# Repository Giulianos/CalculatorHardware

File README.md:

# Programmable Pocket Calculator Hardware

## Description
This programmable pocket sized calculator has the following features:
  - Credit card size, 8mm thick!
  - ARM Cortex M4 Microcontroller
  - microSD card reader
  - OLED Display
  - 44 mechanical* matrix keyboard (*tactile switches)
  - Lipo battery charging circuit

## Images
- Unsoldered, showing it's thickness

- Soldered

- Front view of PCB without tactile switches and with OLED in place

- Back view of PCB unsoldered with battery, micro usb and micro sd card reader in place

- Altium's 3D Render of the PCB

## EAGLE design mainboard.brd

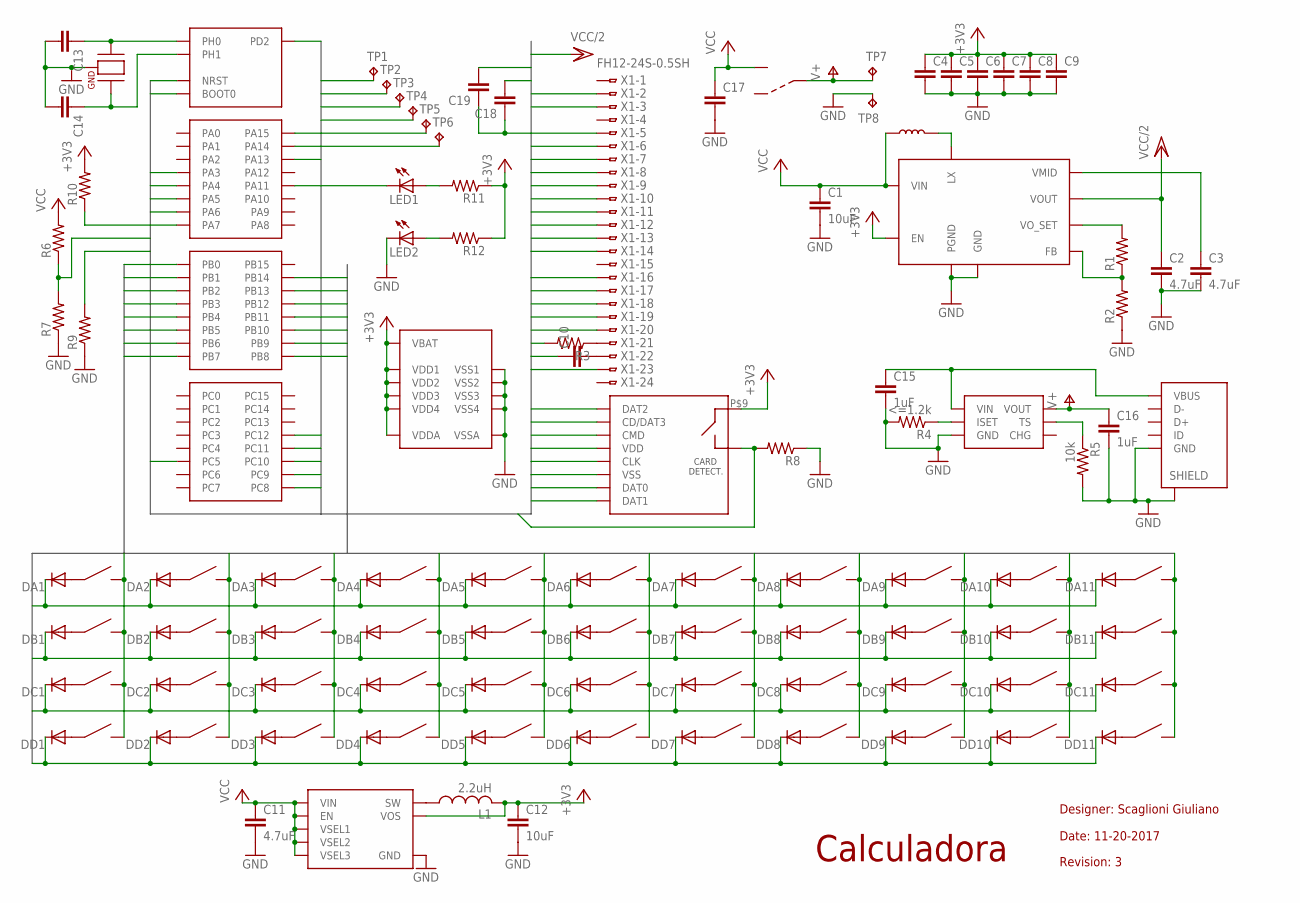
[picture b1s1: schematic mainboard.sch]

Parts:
BTA1, BTA2, BTA3, BTA4, BTA5, BTA6, BTA7, BTA8, BTA9, BTA10, BTA11: WURTH_SWITCH; WURTH_SWITCH_SMD
BTB1, BTB2, BTB3, BTB4, BTB5, BTB6, BTB7, BTB8, BTB9, BTB10, BTB11: WURTH_SWITCH; WURTH_SWITCH_SMD
BTC1, BTC2, BTC3, BTC4, BTC5, BTC6, BTC7, BTC8, BTC9, BTC10, BTC11: WURTH_SWITCH; WURTH_SWITCH_SMD
BTD1, BTD2, BTD3, BTD4, BTD5, BTD6, BTD7, BTD8, BTD9, BTD10, BTD11: WURTH_SWITCH; WURTH_SWITCH_SMD
C1: 10uF; C0805
C2, C3: 4.7uF; C0805
C4, C5, C6, C7, C8, C9, C10, C18, C19: C-EUC0603; C0603
C11: 4.7uF; C0603
C12: 10uF; C0603
C13, C14: CC0603; C0603
C15, C16: 1uF; C0603
C17: CC1206; C1206
DA1, DA2, DA3, DA4, DA5, DA6, DA7, DA8, DA9, DA10, DA11: DIODE-SOD523; SOD523
DB1, DB2, DB3, DB4, DB5, DB6, DB7, DB8, DB9, DB10, DB11: DIODE-SOD523; SOD523
DC1, DC2, DC3, DC4, DC5, DC6, DC7, DC8, DC9, DC10, DC11: DIODE-SOD523; SOD523
DD1, DD2, DD3, DD4, DD5, DD6, DD7, DD8, DD9, DD10, DD11: DIODE-SOD523; SOD523
L1: 2.2uH; L2012C
LED1, LED2: LED_ESML0603; LED_SML0603
R1, R2, R3, R6, R7, R8, R9, R10, R11, R12: R-US_R0402; R0402
R4: <=1.2k; R0402
R5: 10k; R0402
TP1, TP2, TP3, TP4, TP5, TP6, TP7, TP8: TPTP20SQ; TP20SQ
U$1: STM32L471RGT6; LQFP64
U$2: DM3AT-SF-PEJM5; DM3AT-SF-PEJM5_MICROSDREADER
U$3: MOLEX_47346-1001
U$4: STOD1317BTPUR; DFN12L
U$5: VLS252010HBU
U$6: TPS627431YFPR; BGA8
U$7: CX5032SA; CRYSTAL_5X3.2
U$8: BQ21040DBVR; 6-SOT-23
U$9: ALPS_SSSS810701
X1: FH12-24S-0.5SH

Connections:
+3V3: C4.1, C5.1, C6.1, C7.1, C8.1, C9.1, C12.1, C18.2, L1.2, R10.2, R11.1, R12.1, TP1.TP, U$1.P$1 (VBAT), U$1.P$13 (VDDA), U$1.P$19 (VDD1), U$1.P$32 (VDD2), U$1.P$48 (VDD3), U$1.P$64 (VDD4), U$2.P$4 (VDD), U$2.P$9, U$4.P6 (EN), U$6.C2 (VOS), X1.5, X1.9
BAT_SENS: R6.1, R7.2, U$1.P$25 (PC5)
BOOT0: R9.2, TP5.TP, U$1.P$60 (BOOT0)
GND: C1.2, C2.2, C3.2, C4.2, C5.2, C6.2, C7.2, C8.2, C9.2, C10.1, C11.2, C12.2, C13.2, C14.2, C15.2, C16.2, C17.2, C18.1, C19.1, LED2.C, R2.1, R3.2, R4.2, R5.2, R7.1, R8.1, R9.1, TP4.TP, TP8.TP, U$1.P$12 (VSSA), U$1.P$18 (VSS1), U$1.P$31 (VSS2), U$1.P$47 (VSS3), U$1.P$63 (VSS4), U$2.P$6 (VSS), U$3.MECH1, U$3.MECH2, U$3.MECH3, U$3.MECH4, U$3.MECH5, U$3.MECH6, U$3.P$5 (GND), U$4.P4 (GND), U$4.P9 (PGND), U$4.P10 (PGND), U$6.B2 (GND), U$7.P$2 (GND), U$7.P$4 (GND), U$8.P$5 (GND), X1.2, X1.3, X1.6, X1.7, X1.11, X1.12, X1.16, X1.17, X1.18, X1.19, X1.20
KEYCOL0: BTA1.P$2, BTA1.P$4, BTB1.P$2, BTB1.P$4, BTC1.P$2, BTC1.P$4, BTD1.P$2, BTD1.P$4, U$1.P$26 (PB0)
KEYCOL1: BTA2.P$2, BTA2.P$4, BTB2.P$2, BTB2.P$4, BTC2.P$2, BTC2.P$4, BTD2.P$2, BTD2.P$4, U$1.P$27 (PB1)
KEYCOL2: BTA3.P$2, BTA3.P$4, BTB3.P$2, BTB3.P$4, BTC3.P$2, BTC3.P$4, BTD3.P$2, BTD3.P$4, U$1.P$28 (PB2)
KEYCOL3: BTA4.P$2, BTA4.P$4, BTB4.P$2, BTB4.P$4, BTC4.P$2, BTC4.P$4, BTD4.P$2, BTD4.P$4, U$1.P$55 (PB3)
KEYCOL4: BTA5.P$2, BTA5.P$4, BTB5.P$2, BTB5.P$4, BTC5.P$2, BTC5.P$4, BTD5.P$2, BTD5.P$4, U$1.P$56 (PB4)
KEYCOL5: BTA6.P$2, BTA6.P$4, BTB6.P$2, BTB6.P$4, BTC6.P$2, BTC6.P$4, BTD6.P$2, BTD6.P$4, U$1.P$57 (PB5)
KEYCOL6: BTA7.P$2, BTA7.P$4, BTB7.P$2, BTB7.P$4, BTC7.P$2, BTC7.P$4, BTD7.P$2, BTD7.P$4, U$1.P$58 (PB6)
KEYCOL7: BTA8.P$2, BTA8.P$4, BTB8.P$2, BTB8.P$4, BTC8.P$2, BTC8.P$4, BTD8.P$2, BTD8.P$4, U$1.P$59 (PB7)
KEYCOL8: BTA9.P$2, BTA9.P$4, BTB9.P$2, BTB9.P$4, BTC9.P$2, BTC9.P$4, BTD9.P$2, BTD9.P$4, U$1.P$61 (PB8)
KEYCOL9: BTA10.P$2, BTA10.P$4, BTB10.P$2, BTB10.P$4, BTC10.P$2, BTC10.P$4, BTD10.P$2, BTD10.P$4, U$1.P$62 (PB9)
KEYCOL10: BTA11.P$2, BTA11.P$4, BTB11.P$2, BTB11.P$4, BTC11.P$2, BTC11.P$4, BTD11.P$2, BTD11.P$4, U$1.P$29 (PB10)
KEYROW0: DA1.C, DA2.C, DA3.C, DA4.C, DA5.C, DA6.C, DA7.C, DA8.C, DA9.C, DA10.C, DA11.C
KEYROW1: DB1.C, DB2.C, DB3.C, DB4.C, DB5.C, DB6.C, DB7.C, DB8.C, DB9.C, DB10.C, DB11.C, U$1.P$34 (PB13)
KEYROW2: DC1.C, DC2.C, DC3.C, DC4.C, DC5.C, DC6.C, DC7.C, DC8.C, DC9.C, DC10.C, DC11.C, U$1.P$33 (PB12)
KEYROW3: DD1.C, DD2.C, DD3.C, DD4.C, DD5.C, DD6.C, DD7.C, DD8.C, DD9.C, DD10.C, DD11.C, U$1.P$30 (PB11), U$1.P$35 (PB14)
unnamed: U$4.P11 (LX), U$4.P12 (LX), U$5.P$2
unnamed: R1.1, R2.2, U$4.P5 (FB)
unnamed: R3.1, X1.21
unnamed: R1.2, U$4.P3 (VO_SET)
unnamed: C10.2, X1.22
unnamed: C3.1, U$4.P1 (VMID)
unnamed: L1.1, U$6.A1 (SW)
unnamed: BTA1.P$1, BTA1.P$3, DA1.A
unnamed: BTA2.P$1, BTA2.P$3, DA2.A
unnamed: BTA3.P$1, BTA3.P$3, DA3.A
unnamed: BTA4.P$1, BTA4.P$3, DA4.A
unnamed: BTA5.P$1, BTA5.P$3, DA5.A
unnamed: BTA6.P$1, BTA6.P$3, DA6.A
unnamed: BTA7.P$1, BTA7.P$3, DA7.A
unnamed: BTA8.P$1, BTA8.P$3, DA8.A
unnamed: BTA9.P$1, BTA9.P$3, DA9.A
unnamed: BTA10.P$1, BTA10.P$3, DA10.A
unnamed: BTA11.P$1, BTA11.P$3, DA11.A
unnamed: BTB1.P$1, BTB1.P$3, DB1.A
unnamed: BTB2.P$1, BTB2.P$3, DB2.A
unnamed: BTB3.P$1, BTB3.P$3, DB3.A
unnamed: BTB4.P$1, BTB4.P$3, DB4.A
unnamed: BTB5.P$1, BTB5.P$3, DB5.A
unnamed: BTB6.P$1, BTB6.P$3, DB6.A
unnamed: BTB7.P$1, BTB7.P$3, DB7.A
unnamed: BTB8.P$1, BTB8.P$3, DB8.A
unnamed: BTB9.P$1, BTB9.P$3, DB9.A
unnamed: BTB10.P$1, BTB10.P$3, DB10.A
unnamed: BTB11.P$1, BTB11.P$3, DB11.A
unnamed: BTC1.P$1, BTC1.P$3, DC1.A
unnamed: BTC2.P$1, BTC2.P$3, DC2.A
unnamed: BTC3.P$1, BTC3.P$3, DC3.A
unnamed: BTC4.P$1, BTC4.P$3, DC4.A
unnamed: BTC5.P$1, BTC5.P$3, DC5.A
unnamed: BTC6.P$1, BTC6.P$3, DC6.A
unnamed: BTC7.P$1, BTC7.P$3, DC7.A
unnamed: BTC8.P$1, BTC8.P$3, DC8.A
unnamed: BTC9.P$1, BTC9.P$3, DC9.A
unnamed: BTC10.P$1, BTC10.P$3, DC10.A
unnamed: BTC11.P$1, BTC11.P$3, DC11.A
unnamed: BTD1.P$1, BTD1.P$3, DD1.A
unnamed: BTD2.P$1, BTD2.P$3, DD2.A
unnamed: BTD3.P$1, BTD3.P$3, DD3.A
unnamed: BTD4.P$1, BTD4.P$3, DD4.A
unnamed: BTD5.P$1, BTD5.P$3, DD5.A
unnamed: BTD6.P$1, BTD6.P$3, DD6.A
unnamed: BTD7.P$1, BTD7.P$3, DD7.A
unnamed: BTD8.P$1, BTD8.P$3, DD8.A
unnamed: BTD9.P$1, BTD9.P$3, DD9.A
unnamed: BTD10.P$1, BTD10.P$3, DD10.A
unnamed: BTD11.P$1, BTD11.P$3, DD11.A
unnamed: C13.1, U$1.P$5 (PH0), U$7.P$1 (P1)
unnamed: C14.1, U$1.P$6 (PH1), U$7.P$3 (P2)
unnamed: C15.1, U$3.P$1 (VBUS), U$8.P$6 (VIN)
unnamed: R5.1, U$8.P$1 (TS)
unnamed: R4.1, U$8.P$4 (ISET)
unnamed: LED1.A, R11.2
unnamed: LED1.C, U$1.P$44 (PA11)
unnamed: LED2.A, R12.2
NRST: R10.1, TP6.TP, U$1.P$7 (NRST)
PA3: U$1.P$17 (PA3), X1.10
PA13: TP2.TP, U$1.P$46 (PA13)
PA14: TP3.TP, U$1.P$49 (PA14)
SD_CLK: U$1.P$53 (PC12), U$2.P$5 (CLK)
SD_CMD: U$1.P$54 (PD2), U$2.P$3 (CMD)
SD_DAT0: U$1.P$39 (PC8), U$2.P$7 (DAT0)
SD_DAT1: U$1.P$40 (PC9), U$2.P$8 (DAT1)
SD_DAT2: U$1.P$51 (PC10), U$2.P$1 (DAT2)
SD_DAT3: U$1.P$52 (PC11), U$2.P$2 (CD/DAT3)
SD_SWITCH: R8.2, U$1.P$50 (PA15), U$2.P$10
SPI_CS: U$1.P$20 (PA4), X1.8
SPI_MISO: U$1.P$22 (PA6)
SPI_MOSI: U$1.P$23 (PA7), X1.14
SPI_SCK: U$1.P$21 (PA5), X1.13
V+: C16.1, TP7.TP, U$8.P$2 (VOUT), U$9.P$1 (COM)
VCC: C1.1, C11.1, C17.1, R6.2, U$4.P8 (VIN), U$5.P$1, U$6.A2 (VIN), U$6.B1 (EN), U$6.C1 (VSEL1), U$6.D1 (VSEL2), U$6.D2 (VSEL3), U$9.P$3 (L)
VCC/2: C2.1, C19.2, U$4.P2 (VOUT), X1.23

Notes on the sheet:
Calculadora
Designer: Scaglioni Giuliano
Date: 11-20-2017
Revision: 3

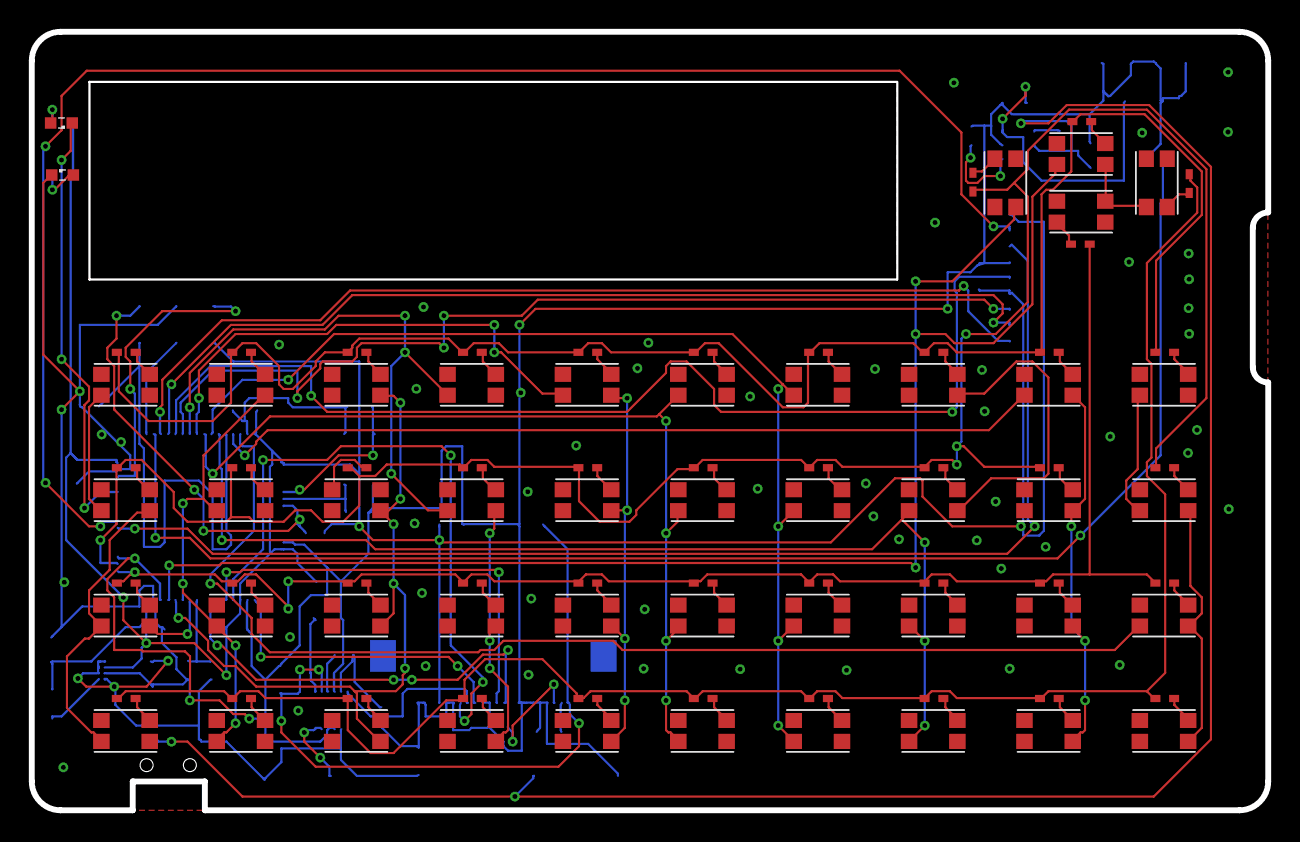
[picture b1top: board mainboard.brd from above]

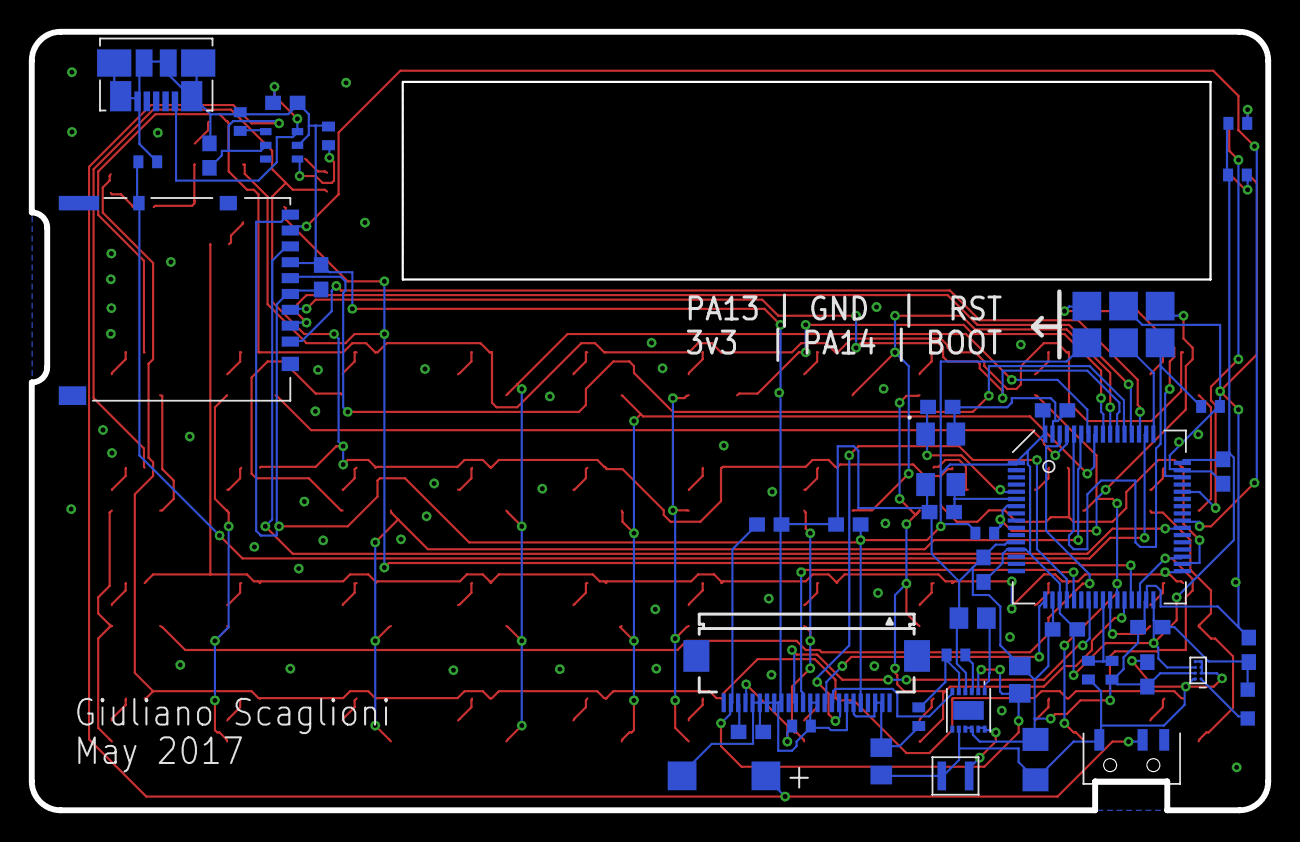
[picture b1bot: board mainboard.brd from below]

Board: 2 copper layers, 85.7 x 54.0 mm, 140 parts (50 on the bottom side), 95 nets.

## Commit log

2016-12-24 Added components
    -Tactile Switch
    -ARM Microcontroller
    -OLED Voltage regulator
2016-12-24 Added components
    -VLS252010HBU Inductor
2016-12-24 Added components
    -Micro SD Reader (Hirose)
    -MicroUSB Connector (Molex)
2016-12-24 Deleted pad mames from symbols
2016-12-25 Started mainboard design
2017-01-06 Added Datasheets
2017-01-06 Added OSHPark DRC
2017-01-06 Features added in schematic
    Power supplies (+3.3 and 12v)
    Button matrix
    Microprocessor and support circuitry
    Programming headers
    SD Card reader
    OLED Screen connector
2017-01-06 Initial component placement
2017-01-06 Added components
2017-01-07 [Rev1] Finished shematic design
    Added usb charging
    PWR Button
2017-01-07 [Rev1] Finished board
2017-01-07 Modified silkscreen
2017-01-16 Fixed Issues/New features
    Battery level sensing
    microSD card sensing
    Fixed issues:
    Boot0 pulldown resistor
    NRST pullup resistor
2017-01-16 Updated PCB
2017-02-20 Minor Stetic Modifications
    DIN-A4 frame in schematic and relocation.
2017-02-20 Misc Files Added
    BOM
    PCB Renders
    PCB 3D models
    etc..
2017-04-12 Added overlay
2017-05-22 [FIX] Missing EN connection in STOD1317BTPUR
    Conected EN Pin in STOD1317BTPUR to 3v3
    Added 0402 led for tests.
    Moved components from bga8 chip to allow visual inspection of soldering.
2017-05-22 Added Silkscreen
2017-05-23 Added GCalc Logo and Ground Plane
2017-09-13 Added images for readme
2017-11-20 Finished rev 3 schematic and component placement
2017-11-21 Finished Rev 6 pcb routing
